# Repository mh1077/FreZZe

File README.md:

# FreZZe
Fremo Zeit Zeichenempfänger

Das ist ein Zeitzeichen Empfänger für das MRClock Protokoll. Es empfängt MRClock Datentelegramme (Multicast) auf dem WLAN. Der Zeitzeichenempfänger 
wandelt die empfangenen Telegramme um, sodass eine Nebenuhrlinie mit mehreren Uhren betrieben werden kann. Eine Anzeige für Uhr läuft / steht kann realisiert werden, z.B. mit einer rot/grün Ampel aus der Fertigungstechnik.

Viel Spass beim Nachbauen

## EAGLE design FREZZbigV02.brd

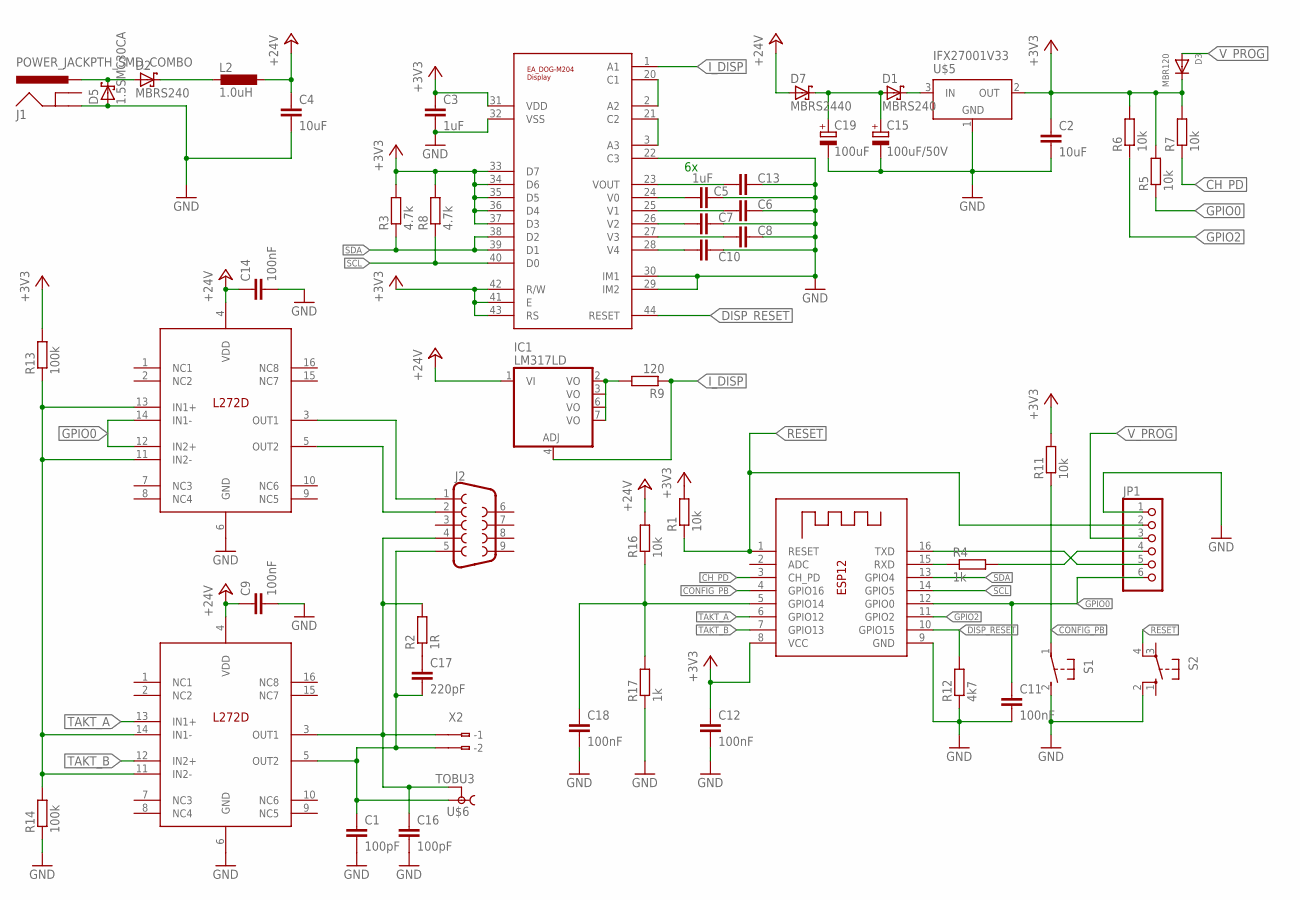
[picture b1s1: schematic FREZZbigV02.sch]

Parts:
C1, C16: 100pF; C0603K
C2: 10uF; C0603K
C3, C5, C6, C7, C8, C10, C13: 1uF; C0603K
C4: 10uF; C1210K
C9, C11, C12, C14, C18: 100nF; C0603K
C15: 100uF/50V; PANASONIC_F
C17: 220pF; C0603K
C19: 100uF; E7,5-18
D1, D2: MBRS240; SMB
D3: MBR120; SOD-123
D5: 1.5SMC30CA; SMC
D7: MBRS2440; SMB
IC1: LM317LD; SO08
J1: POWER_JACKPTH_SMD_COMBO; POWER_JACK_COMBO
J2: DB9FEMALE; DB9
JP1: PINHD-1X6; 1X06
L2: 1.0uH; L3230M
R1, R5, R6, R7, R11, R16: 10k; M1206
R2: 1R; M1206
R3, R8: 4.7k; M1206
R4, R17: 1k; M1206
R9: 120; M1206
R12: 4k7; M1206
R13, R14: 100k; M1206
S1: 31-XX; B3F-31XX
S2: 10-XX; B3F-10XX
U$1: EA_DOG-M204-DISPLAY; E_DOG-M204_DISPLAY
U$2, U$3: L272D; SO16
U$5: IFX27001V33; TO252
U$6: TOBU3; TOBU3-REICHELT
X1: ESP-12
X2: 233-102

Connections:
$N122: D1.C, U$5.3 (IN)
+3V3: C2.1, C3.1, C12.1, D3.C, R1.2, R3.2, R5.2, R6.2, R7.2, R8.2, R11.2, R13.2, U$1.31 (VDD), U$1.33 (D7), U$1.34 (D6), U$1.35 (D5), U$1.36 (D4), U$1.37 (D3), U$1.41 (E), U$1.42 (R/W), U$1.43 (RS), U$5.2 (OUT), X1.8 (VCC)
+24V: C4.1, C9.1, C14.1, D7.A, IC1.1 (VI), L2.1, R16.2, U$2.4 (VDD), U$3.4 (VDD)
CH_PD: R7.1, X1.3 (CH_PD)
CONFIG_PB: R11.1, S1.1, X1.4 (GPIO16)
DISP_RESET: R12.2, U$1.44 (RESET), X1.10 (GPIO15)
GND: C1.2, C2.2, C3.2, C4.2, C5.1, C6.1, C7.1, C8.1, C9.2, C10.1, C11.2, C12.2, C13.1, C14.2, C15.-, C16.2, C18.2, C19.-, D5.A, J1.GND@1 (GND), JP1.1, R12.1, R14.1, R17.1, S1.2 (S), S2.2 (S1), U$1.22 (C3), U$1.29 (IM2), U$1.30 (IM1), U$1.32 (VSS), U$2.6 (GND), U$3.6 (GND), U$5.1 (GND), X1.9 (GND)
GPIO0: C11.1, JP1.6, R5.1, U$3.12 (IN2+), U$3.14 (IN1-), X1.12 (GPIO0)
GPIO2: R6.1, X1.11 (GPIO2)
I_DISP: IC1.4 (ADJ), R9.1, U$1.1 (A1)
unnamed: JP1.5, X1.16 (TXD)
unnamed: JP1.4, R4.2
unnamed: R4.1, X1.15 (RXD)
unnamed: C13.2, U$1.23 (VOUT)
unnamed: D2.A, D5.C, J1.POWER (PWR)
unnamed: C5.2, U$1.24 (V0)
unnamed: D2.C, L2.2
unnamed: C15.+, C19.+, D1.A, D7.C
unnamed: C17.1, R2.1
unnamed: C16.1, J2.4, R2.2, U$2.3 (OUT1), U$6.2, U$6.2@1 (2), U$6.2@2 (2), X2.B1 (B-1)
unnamed: C6.2, U$1.25 (V1)
unnamed: C1.1, C17.2, J2.5, U$2.5 (OUT2), U$6.1, X2.B2 (B-2)
unnamed: C7.2, U$1.26 (V2)
unnamed: C8.2, U$1.27 (V3)
unnamed: C10.2, U$1.28 (V4)
unnamed: U$1.3 (A3), U$1.21 (C2)
unnamed: U$1.2 (A2), U$1.20 (C1)
unnamed: IC1.2 (VO), IC1.3 (VO), IC1.6 (VO), IC1.7 (VO), R9.2
unnamed: J2.1, U$3.3 (OUT1)
unnamed: J2.2, U$3.5 (OUT2)
unnamed: R13.1, R14.2, U$2.11 (IN2-), U$2.14 (IN1-), U$3.11 (IN2-), U$3.13 (IN1+)
RESET: JP1.2, R1.1, S2.4 (P1), X1.1 (RESET)
SCL: R8.1, U$1.40 (D0), X1.14 (GPIO5)
SDA: R3.1, U$1.38 (D2), U$1.39 (D1), X1.13 (GPIO4)
SHDN: C18.1, R16.1, R17.2, X1.5 (GPIO14)
TAKT_A: U$2.13 (IN1+), X1.6 (GPIO12)
TAKT_B: U$2.12 (IN2+), X1.7 (GPIO13)
V_PROG: D3.A, JP1.3

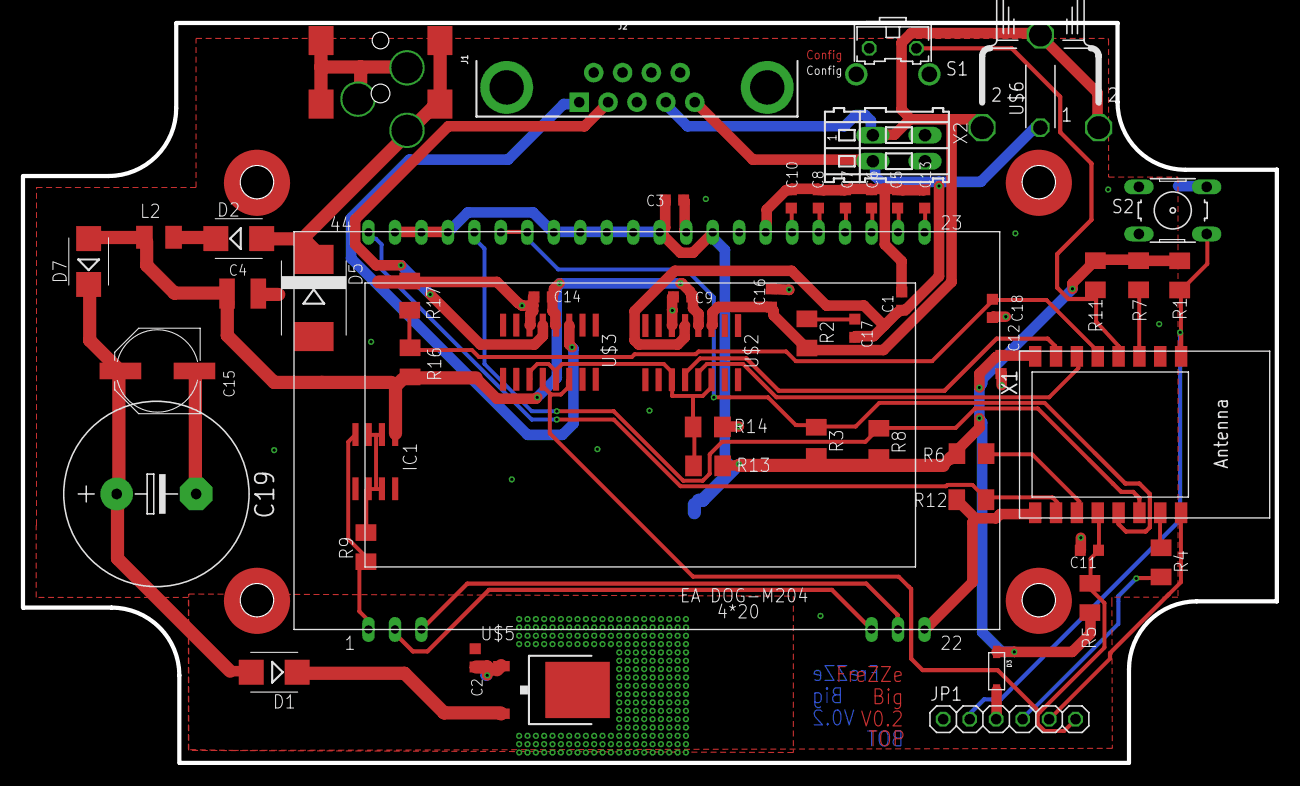
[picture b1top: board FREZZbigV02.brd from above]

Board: 2 copper layers, 120.3 x 71.0 mm, 53 parts (0 on the bottom side), 38 nets.

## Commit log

2019-09-18 Add files via upload
    Bauteileliste
2019-09-22 Update Partlist_FREZZEV02
2023-07-03 New Version
    - added NTP Function,
    - change to PlatformIO and VSCode

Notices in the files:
parts and their libraries:
SparkFun-Connectors: Licensing: Creative Commons ShareAlike 4.0 International - https://creativecommons.org/licenses/by-sa/4.0
